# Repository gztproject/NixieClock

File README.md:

# NixieClock

* Install VS Code
  * Install PlatformIO
* Clone/download this repo
* Open with VS Code/PlatformIO
* Copy config_override_example.h to config_override.h
  * Edit settings in config_override.h
* Build and upload to your ESP8266

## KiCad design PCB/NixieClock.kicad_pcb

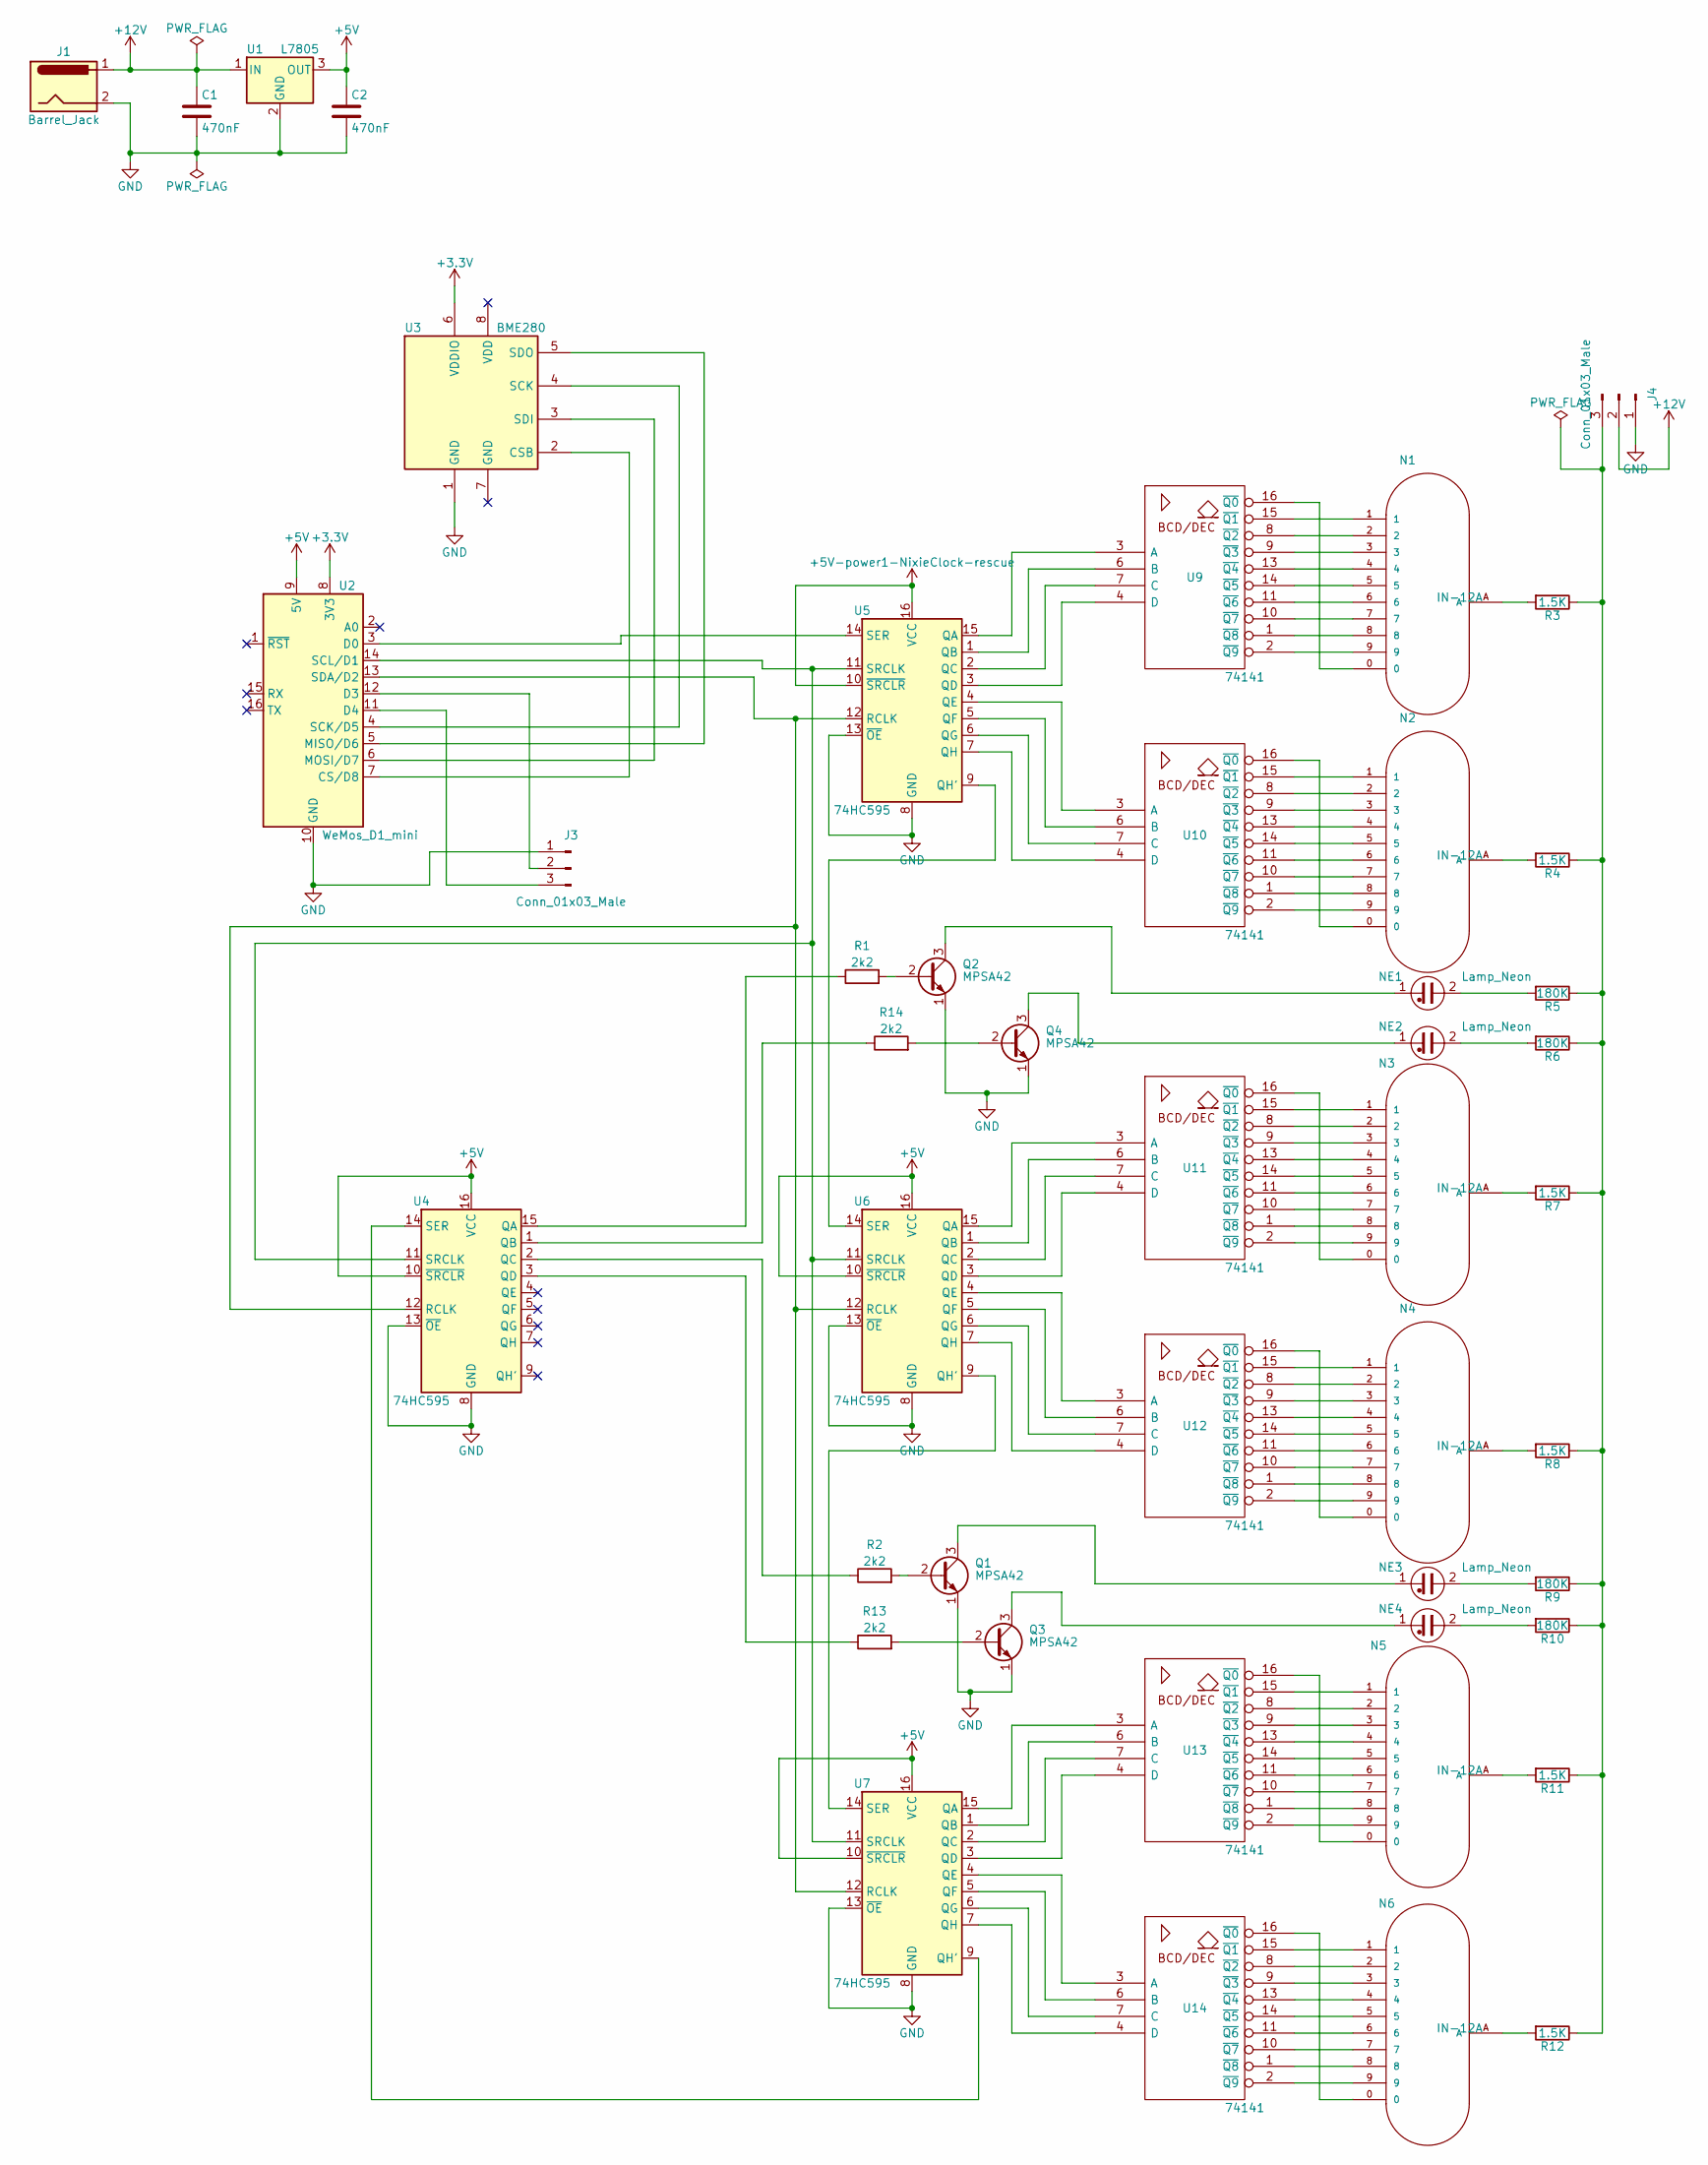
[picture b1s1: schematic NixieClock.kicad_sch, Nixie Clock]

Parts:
C1, C2: 470nF; C_Disc_D5.0mm_W2.5mm_P5.00mm
J1: Barrel_Jack; BARREL_JACK
J3, J4: Conn_01x03_Male; JST_EH_B03B-EH-A_03x2.50mm_Straight
N1, N2, N3, N4, N5, N6: IN-12A; IN-12-DSUB
NE1, NE2, NE3, NE4: Lamp_Neon; NE2-NEON-BULB-DRILL
Q1, Q2, Q3, Q4: MPSA42; TO-92_Inline_Narrow_Oval
R1, R2, R13, R14: 2k2; R_Axial_DIN0207_L6.3mm_D2.5mm_P10.16mm_Horizontal
R3, R4, R7, R8, R11, R12: 1.5K; R_Axial_DIN0207_L6.3mm_D2.5mm_P10.16mm_Horizontal
R5, R6, R9, R10: 180K; R_Axial_DIN0207_L6.3mm_D2.5mm_P10.16mm_Horizontal
U1: L7805; TO-220-3_Vertical
U2: WeMos_D1_mini; Pololu_Breakout-16_15.2x20.3mm
U3: BME280; PinHeader_1x06_P2.54mm_Horizontal
U4, U5, U6, U7: 74HC595; DIP-16_W7.62mm_LongPads
U9, U10, U11, U12, U13, U14: 74141; DIP-16_W7.62mm_LongPads

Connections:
+3V3: U2.8 (3V3), U3.6 (VDDIO)
+12V: C1.1, J1.1, J4.2, U1.1 (IN)
GND: C1.2, C2.2, J1.2, J3.1, J4.1, Q1.1 (E), Q2.1 (E), Q3.1 (E), Q4.1 (E), U1.2 (GND), U2.10 (GND), U3.1 (GND), U4.8 (GND), U4.13 (~OE), U5.8 (GND), U5.13 (~OE), U6.8 (GND), U6.13 (~OE), U7.8 (GND), U7.13 (~OE), U9.12 (GND), U10.12 (GND), U11.12 (GND), U12.12 (GND), U13.12 (GND), U14.12 (GND)
unnamed: J3.2, U2.12 (D3)
unnamed: J3.3, U2.11 (D4)
unnamed: J4.3, R3.1, R4.1, R5.1, R6.1, R7.1, R8.1, R9.1, R10.1, R11.1, R12.1
unnamed: N1.0, U9.16 (~Q0)
unnamed: N1.1, U9.15 (~Q1)
unnamed: N1.2, U9.8 (~Q2)
unnamed: N1.3, U9.9 (~Q3)
unnamed: N1.4, U9.13 (~Q4)
unnamed: N1.5, U9.14 (~Q5)
unnamed: N1.6, U9.11 (~Q6)
unnamed: N1.7, U9.10 (~Q7)
unnamed: N1.8, U9.1 (~Q8)
unnamed: N1.9, U9.2 (~Q9)
unnamed: N1.A, R3.2
unnamed: N2.0, U10.16 (~Q0)
unnamed: N2.1, U10.15 (~Q1)
unnamed: N2.2, U10.8 (~Q2)
unnamed: N2.3, U10.9 (~Q3)
unnamed: N2.4, U10.13 (~Q4)
unnamed: N2.5, U10.14 (~Q5)
unnamed: N2.6, U10.11 (~Q6)
unnamed: N2.7, U10.10 (~Q7)
unnamed: N2.8, U10.1 (~Q8)
unnamed: N2.9, U10.2 (~Q9)
unnamed: N2.A, R4.2
unnamed: N3.0, U11.16 (~Q0)
unnamed: N3.1, U11.15 (~Q1)
unnamed: N3.2, U11.8 (~Q2)
unnamed: N3.3, U11.9 (~Q3)
unnamed: N3.4, U11.13 (~Q4)
unnamed: N3.5, U11.14 (~Q5)
unnamed: N3.6, U11.11 (~Q6)
unnamed: N3.7, U11.10 (~Q7)
unnamed: N3.8, U11.1 (~Q8)
unnamed: N3.9, U11.2 (~Q9)
unnamed: N3.A, R7.2
unnamed: N4.0, U12.16 (~Q0)
unnamed: N4.1, U12.15 (~Q1)
unnamed: N4.2, U12.8 (~Q2)
unnamed: N4.3, U12.9 (~Q3)
unnamed: N4.4, U12.13 (~Q4)
unnamed: N4.5, U12.14 (~Q5)
unnamed: N4.6, U12.11 (~Q6)
unnamed: N4.7, U12.10 (~Q7)
unnamed: N4.8, U12.1 (~Q8)
unnamed: N4.9, U12.2 (~Q9)
unnamed: N4.A, R8.2
unnamed: N5.0, U13.16 (~Q0)
unnamed: N5.1, U13.15 (~Q1)
unnamed: N5.2, U13.8 (~Q2)
unnamed: N5.3, U13.9 (~Q3)
unnamed: N5.4, U13.13 (~Q4)
unnamed: N5.5, U13.14 (~Q5)
unnamed: N5.6, U13.11 (~Q6)
unnamed: N5.7, U13.10 (~Q7)
unnamed: N5.8, U13.1 (~Q8)
unnamed: N5.9, U13.2 (~Q9)
unnamed: N5.A, R11.2
unnamed: N6.0, U14.16 (~Q0)
unnamed: N6.1, U14.15 (~Q1)
unnamed: N6.2, U14.8 (~Q2)
unnamed: N6.3, U14.9 (~Q3)
unnamed: N6.4, U14.13 (~Q4)
unnamed: N6.5, U14.14 (~Q5)
unnamed: N6.6, U14.11 (~Q6)
unnamed: N6.7, U14.10 (~Q7)
unnamed: N6.8, U14.1 (~Q8)
unnamed: N6.9, U14.2 (~Q9)
unnamed: N6.A, R12.2
unnamed: NE1.1, Q2.3 (C)
unnamed: NE1.2, R5.2
unnamed: NE2.1, Q4.3 (C)
unnamed: NE2.2, R6.2
unnamed: NE3.1, Q1.3 (C)
unnamed: NE3.2, R9.2
unnamed: NE4.1, Q3.3 (C)
unnamed: NE4.2, R10.2
unnamed: Q1.2 (B), R2.2
unnamed: Q2.2 (B), R1.2
unnamed: Q3.2 (B), R13.2
unnamed: Q4.2 (B), R14.2
unnamed: U2.3 (D0), U5.14 (SER)
unnamed: U2.4 (SCK/D5), U3.4 (SCK)
unnamed: U2.5 (MISO/D6), U3.5 (SDO)
unnamed: U2.6 (MOSI/D7), U3.3 (SDI)
unnamed: U2.7 (CS/D8), U3.2 (CSB)
unnamed: U2.13 (SDA/D2), U4.12 (RCLK), U5.12 (RCLK), U6.12 (RCLK), U7.12 (RCLK)
unnamed: U2.14 (SCL/D1), U4.11 (SRCLK), U5.11 (SRCLK), U6.11 (SRCLK), U7.11 (SRCLK)
unnamed: R14.1, U4.1 (QB)
unnamed: R2.1, U4.2 (QC)
unnamed: R13.1, U4.3 (QD)
unnamed: U4.14 (SER), U7.9 (QH')
unnamed: R1.1, U4.15 (QA)
unnamed: U5.1 (QB), U9.6 (B)
unnamed: U5.2 (QC), U9.7 (C)
unnamed: U5.3 (QD), U9.4 (D)
unnamed: U5.9 (QH'), U6.14 (SER)
unnamed: U5.15 (QA), U9.3 (A)
unnamed: U6.9 (QH'), U7.14 (SER)
unnamed: U5.4 (QE), U10.3 (A)
unnamed: U5.7 (QH), U10.4 (D)
unnamed: U5.5 (QF), U10.6 (B)
unnamed: U5.6 (QG), U10.7 (C)
unnamed: U6.15 (QA), U11.3 (A)
unnamed: U6.3 (QD), U11.4 (D)
unnamed: U6.1 (QB), U11.6 (B)
unnamed: U6.2 (QC), U11.7 (C)
unnamed: U6.4 (QE), U12.3 (A)
unnamed: U6.7 (QH), U12.4 (D)
unnamed: U6.5 (QF), U12.6 (B)
unnamed: U6.6 (QG), U12.7 (C)
unnamed: U7.15 (QA), U13.3 (A)
unnamed: U7.3 (QD), U13.4 (D)
unnamed: U7.1 (QB), U13.6 (B)
unnamed: U7.2 (QC), U13.7 (C)
unnamed: U7.4 (QE), U14.3 (A)
unnamed: U7.7 (QH), U14.4 (D)
unnamed: U7.5 (QF), U14.6 (B)
unnamed: U7.6 (QG), U14.7 (C)

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
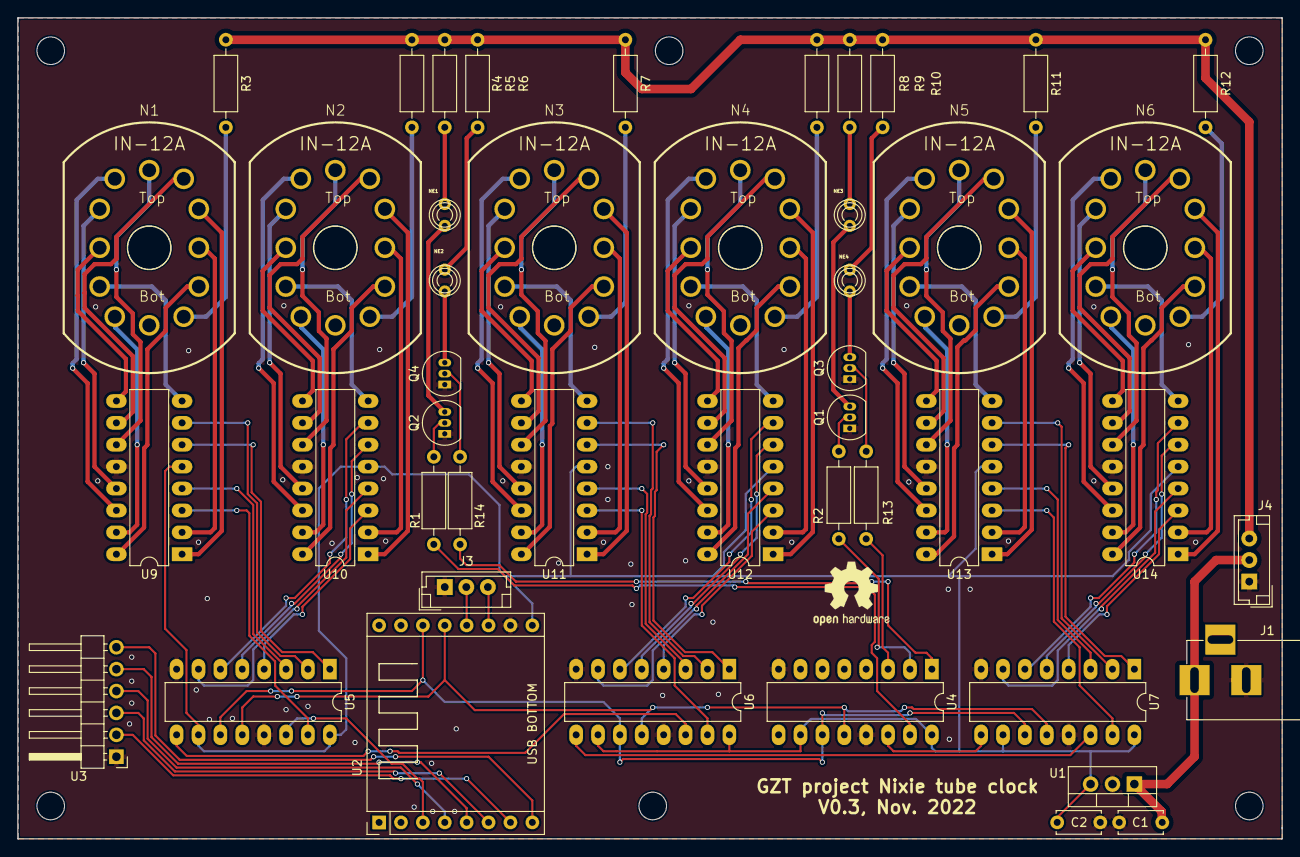
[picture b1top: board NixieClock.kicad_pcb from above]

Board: 2 copper layers, 146.7 x 95.2 mm, 46 parts (0 on the bottom side), 123 nets.

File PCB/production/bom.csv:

Designator,Footprint,Quantity,Value,LCSC Part #
"C1, C2",C_Disc_D5.0mm_W2.5mm_P5.00mm,2,470nF,
J1,BARREL_JACK,1,Barrel_Jack,
"J3, J4",JST_EH_B03B-EH-A_03x2.50mm_Straight,2,Conn_01x03_Male,
"N1, N2, N3, N4, N5, N6",IN-12-DSUB,6,IN-12A,
"NE1, NE2, NE3, NE4",NE2-NEON-BULB-DRILL,4,Lamp_Neon,
"Q1, Q2, Q3, Q4",TO-92_Inline_Narrow_Oval,4,MPSA42,
"R1, R13, R14, R2",R_Axial_DIN0207_L6.3mm_D2.5mm_P10.16mm_Horizontal,4,2k2,
"R10, R5, R6, R9",R_Axial_DIN0207_L6.3mm_D2.5mm_P10.16mm_Horizontal,4,180K,
"R11, R12, R3, R4, R7, R8",R_Axial_DIN0207_L6.3mm_D2.5mm_P10.16mm_Horizontal,6,1.5K,
U1,TO-220-3_Vertical,1,L7805,
"U10, U11, U12, U13, U14, U9",DIP-16_W7.62mm_LongPads,6,74141,
U2,Pololu_Breakout-16_15.2x20.3mm,1,WeMos_D1_mini,
U3,PinHeader_1x06_P2.54mm_Horizontal,1,BME280,
"U4, U5, U6, U7",DIP-16_W7.62mm_LongPads,4,74HC595,

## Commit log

2019-12-08 Put custom libs in proper dirs
2019-12-10 Some basic work and functions
2019-12-10 A fix in CycleTubes routine
2019-12-12 Import file check
2019-12-12 Updated lib_dep
2019-12-12 Started work on DST
    Added config parameters and some objects
2019-12-14 More work on DST
2019-12-15 Some updates in config
2019-12-15 A fix in config
2019-12-15 A fix in auto build testing
2019-12-15 Implemented automatic DST changes
2020-01-31 Added PCB
2020-01-31 PCB top fill
2020-02-06 Some PCB fixes
2020-02-06 Updates for new 74HC595 library
2020-03-13 Updated PCB files
2020-03-22 Reduced update rate, added RNG to cycleTubes()
2020-05-07 Showing the clock's IP
2022-11-04 Fixed issue #2 - added base resistors, layout touch-ups
2024-05-23 Small fixes, gitignore
